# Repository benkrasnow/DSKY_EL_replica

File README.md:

# DSKY_EL_replica
Schematic, PCB layout, mechanical CAD, and firmware to create a replica of the DSKY with electroluminescent display
https://www.youtube.com/watch?v=Z2o_Sp2-aBo

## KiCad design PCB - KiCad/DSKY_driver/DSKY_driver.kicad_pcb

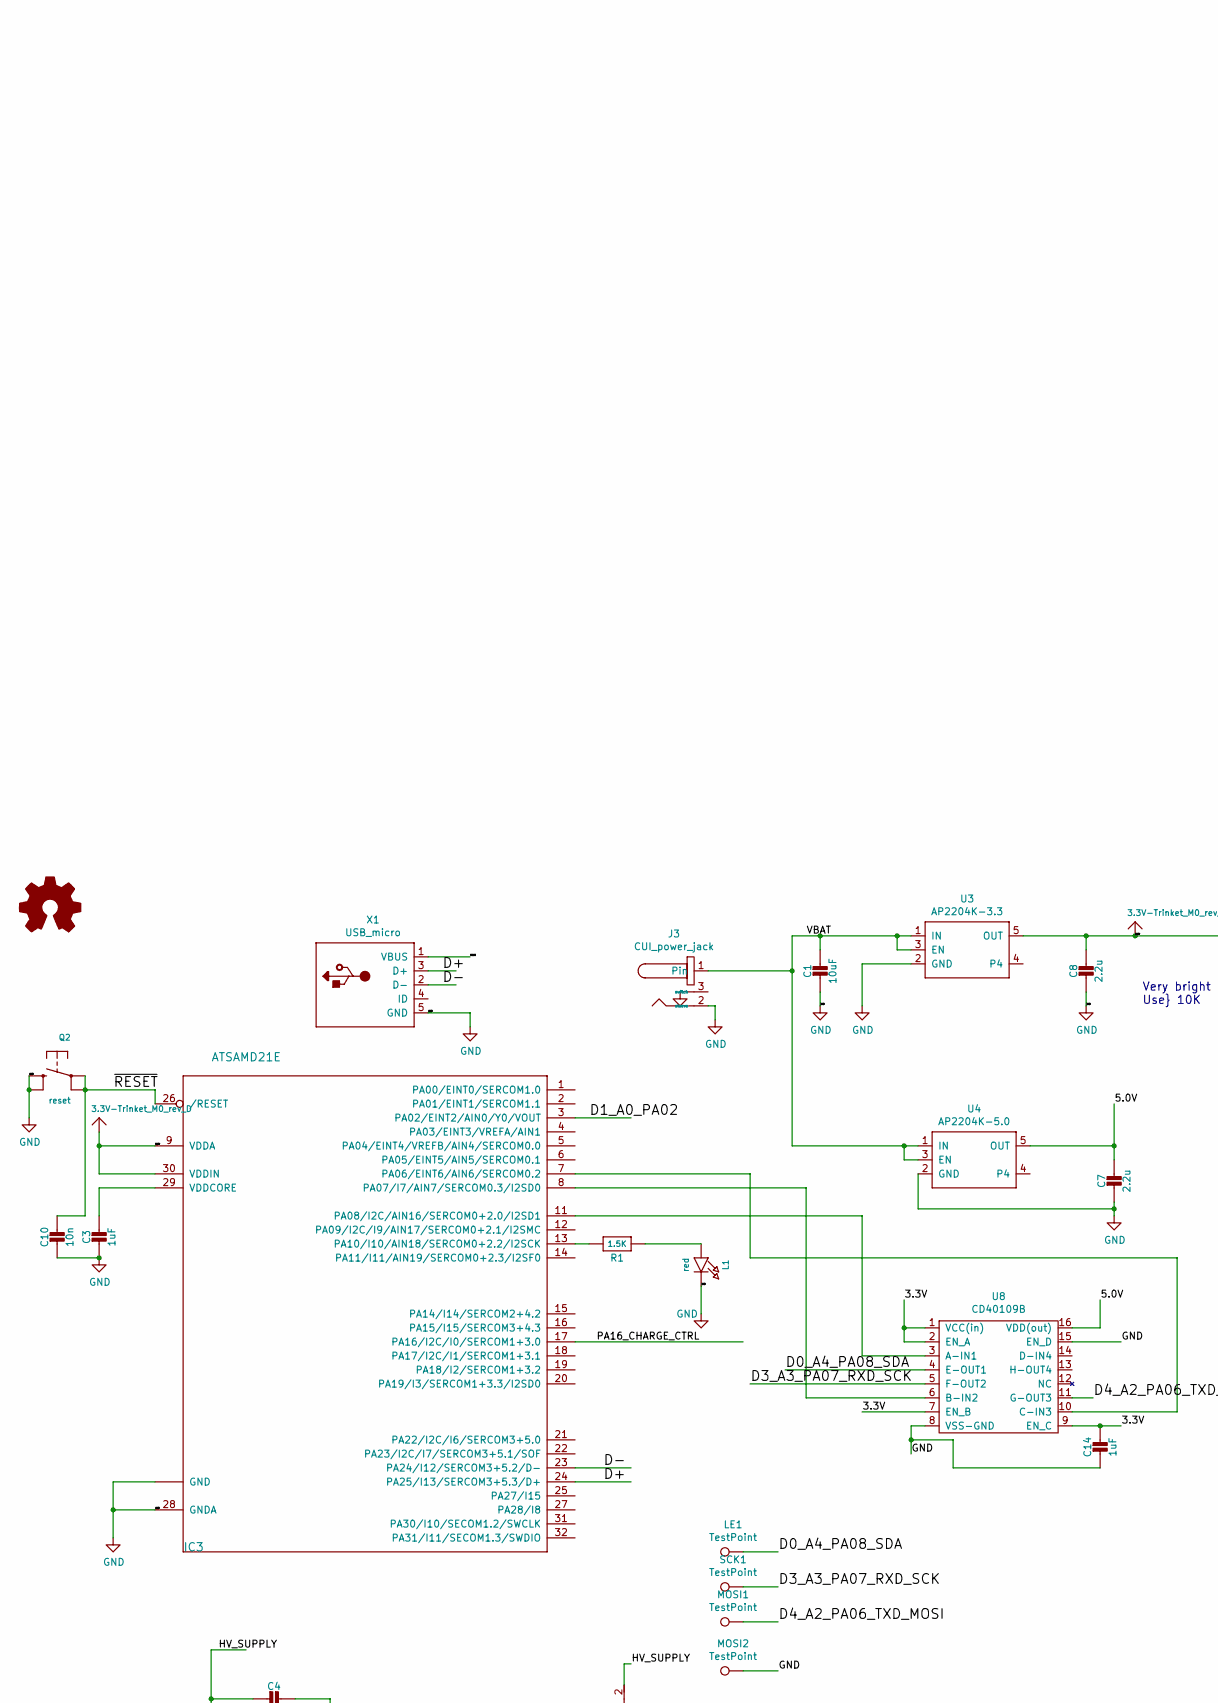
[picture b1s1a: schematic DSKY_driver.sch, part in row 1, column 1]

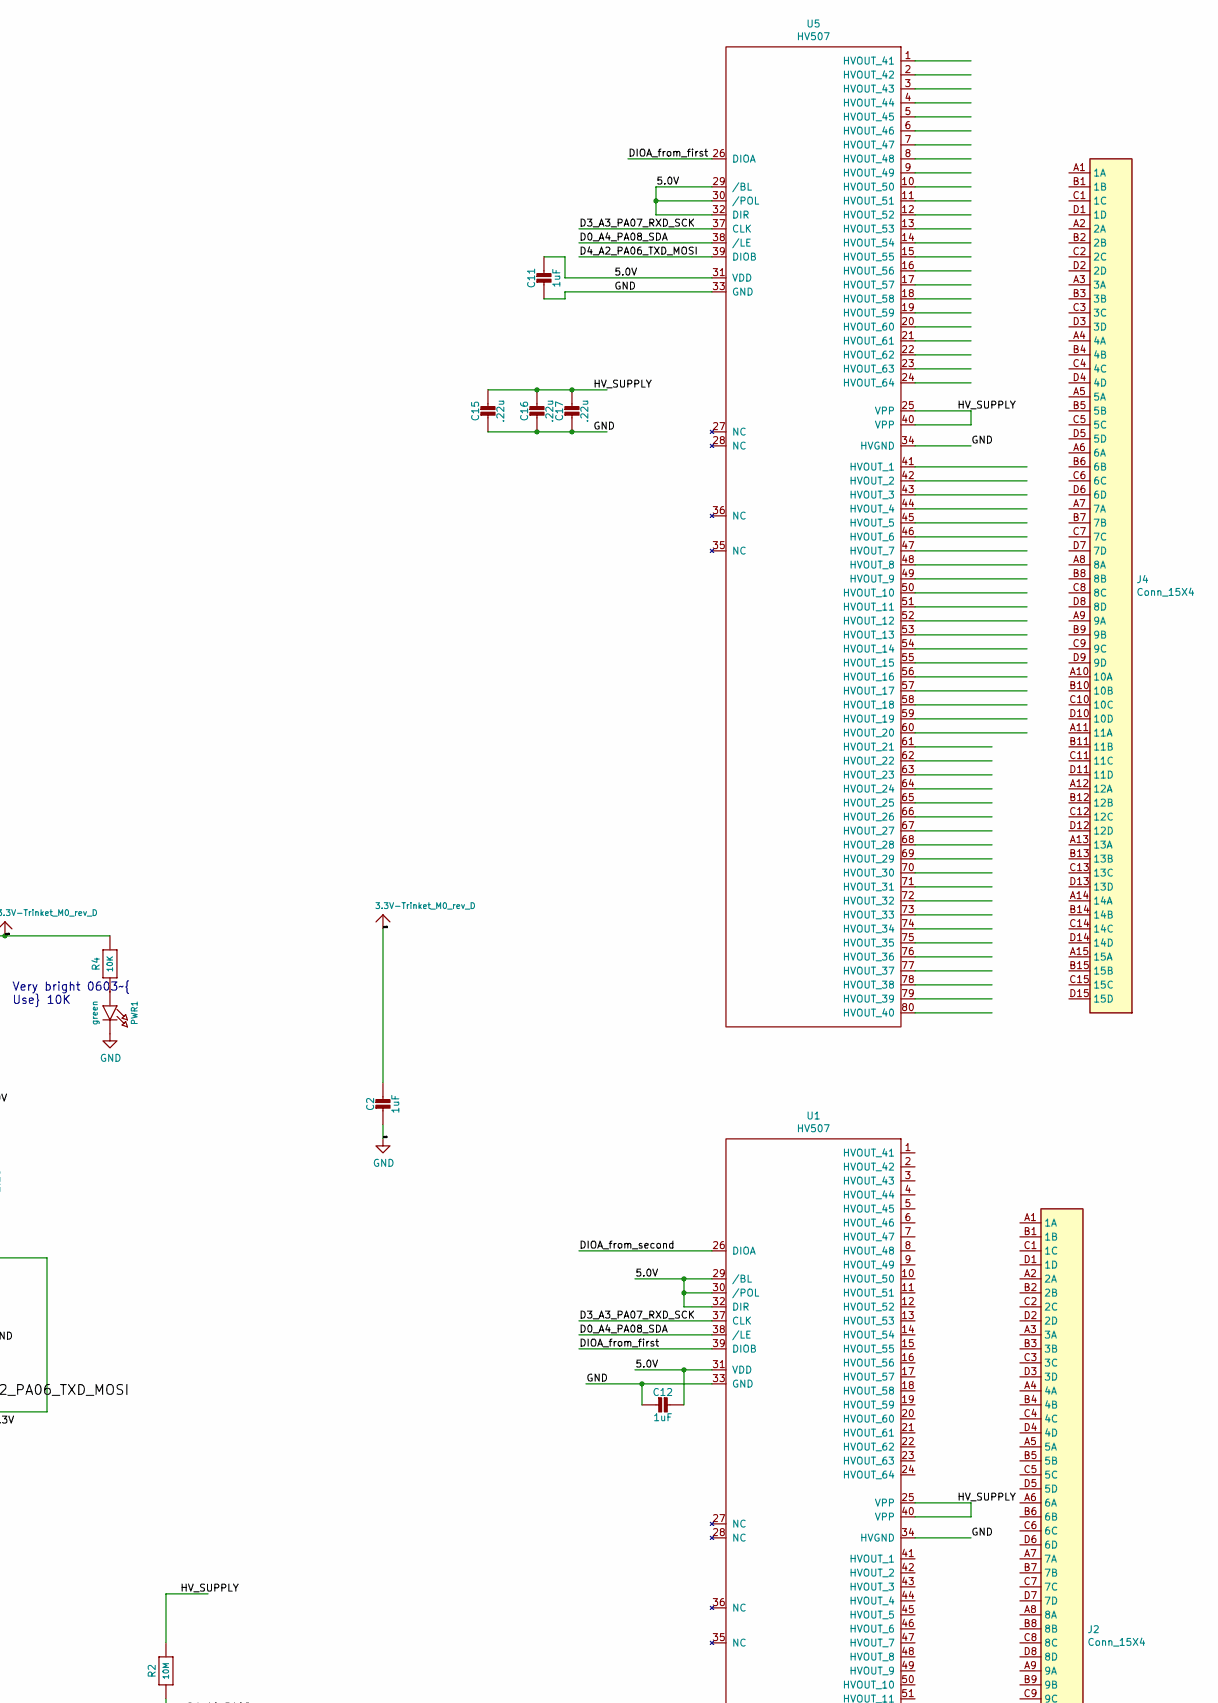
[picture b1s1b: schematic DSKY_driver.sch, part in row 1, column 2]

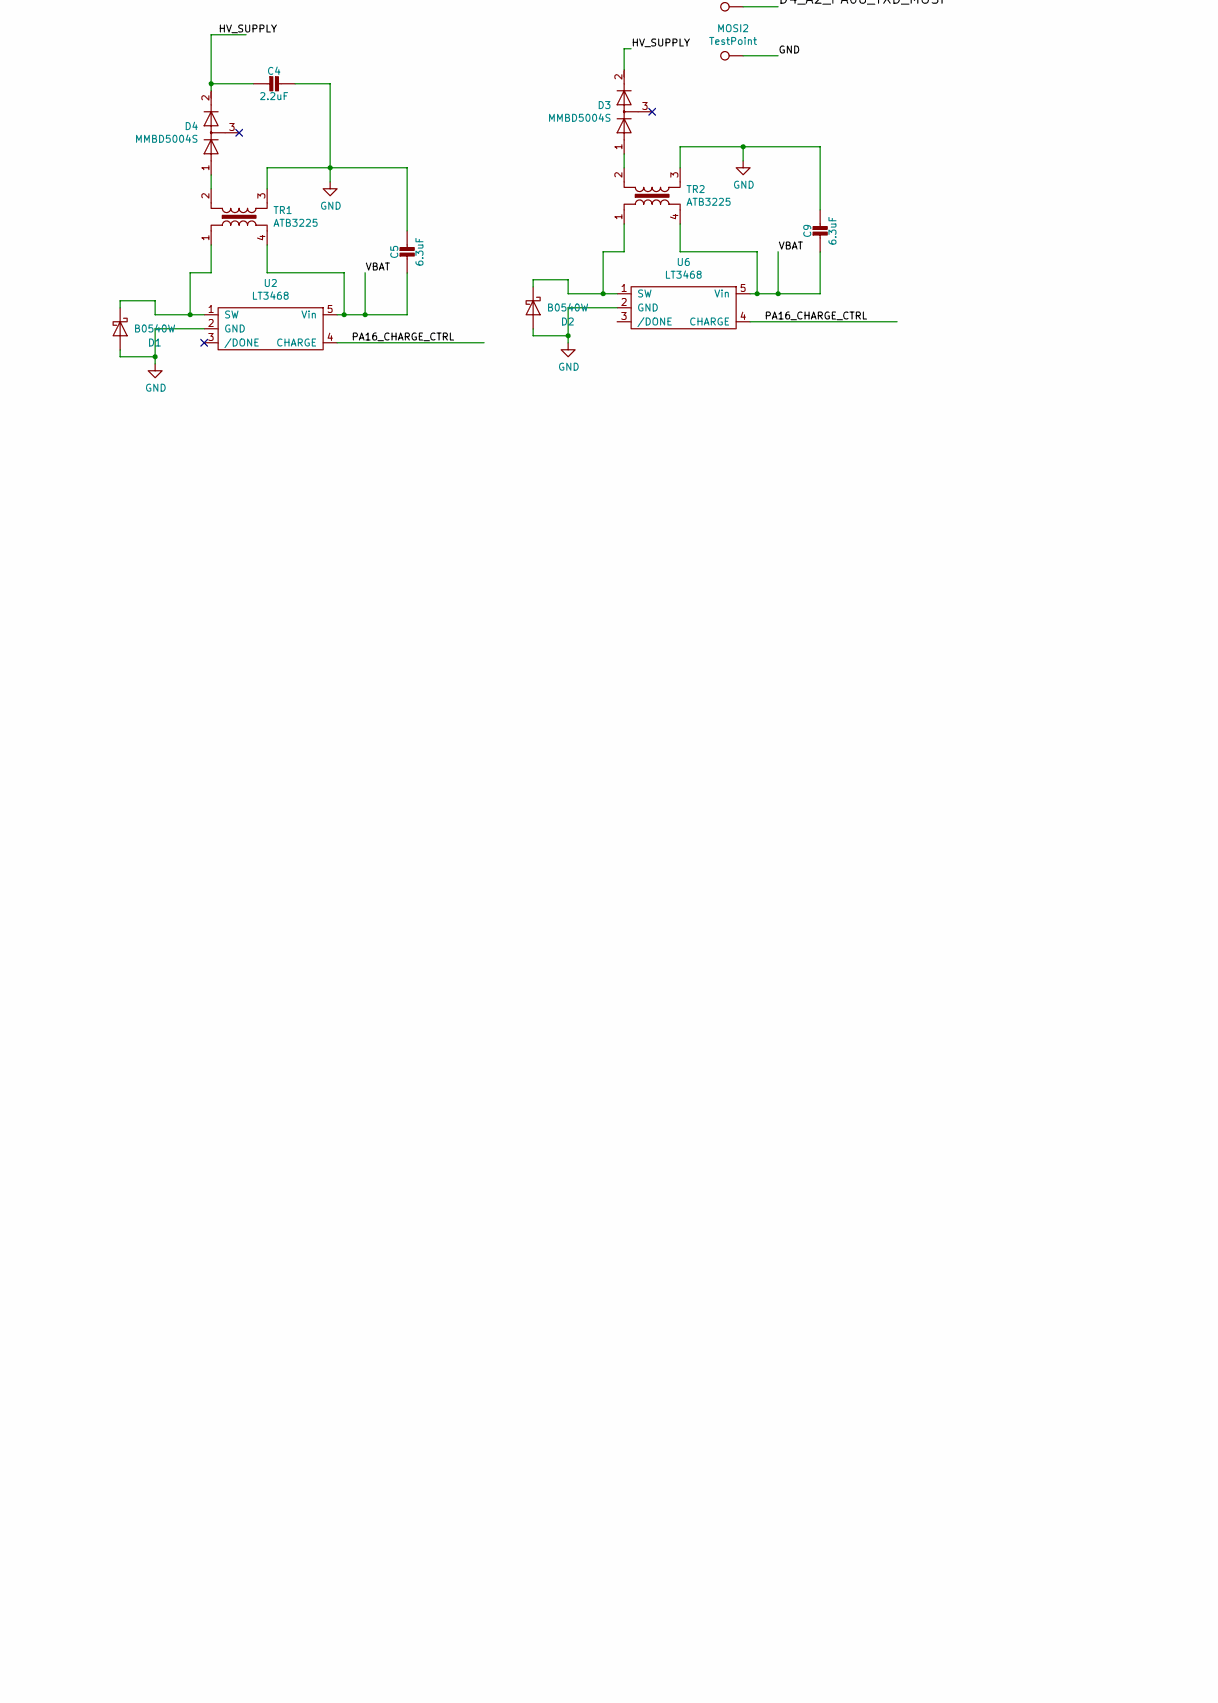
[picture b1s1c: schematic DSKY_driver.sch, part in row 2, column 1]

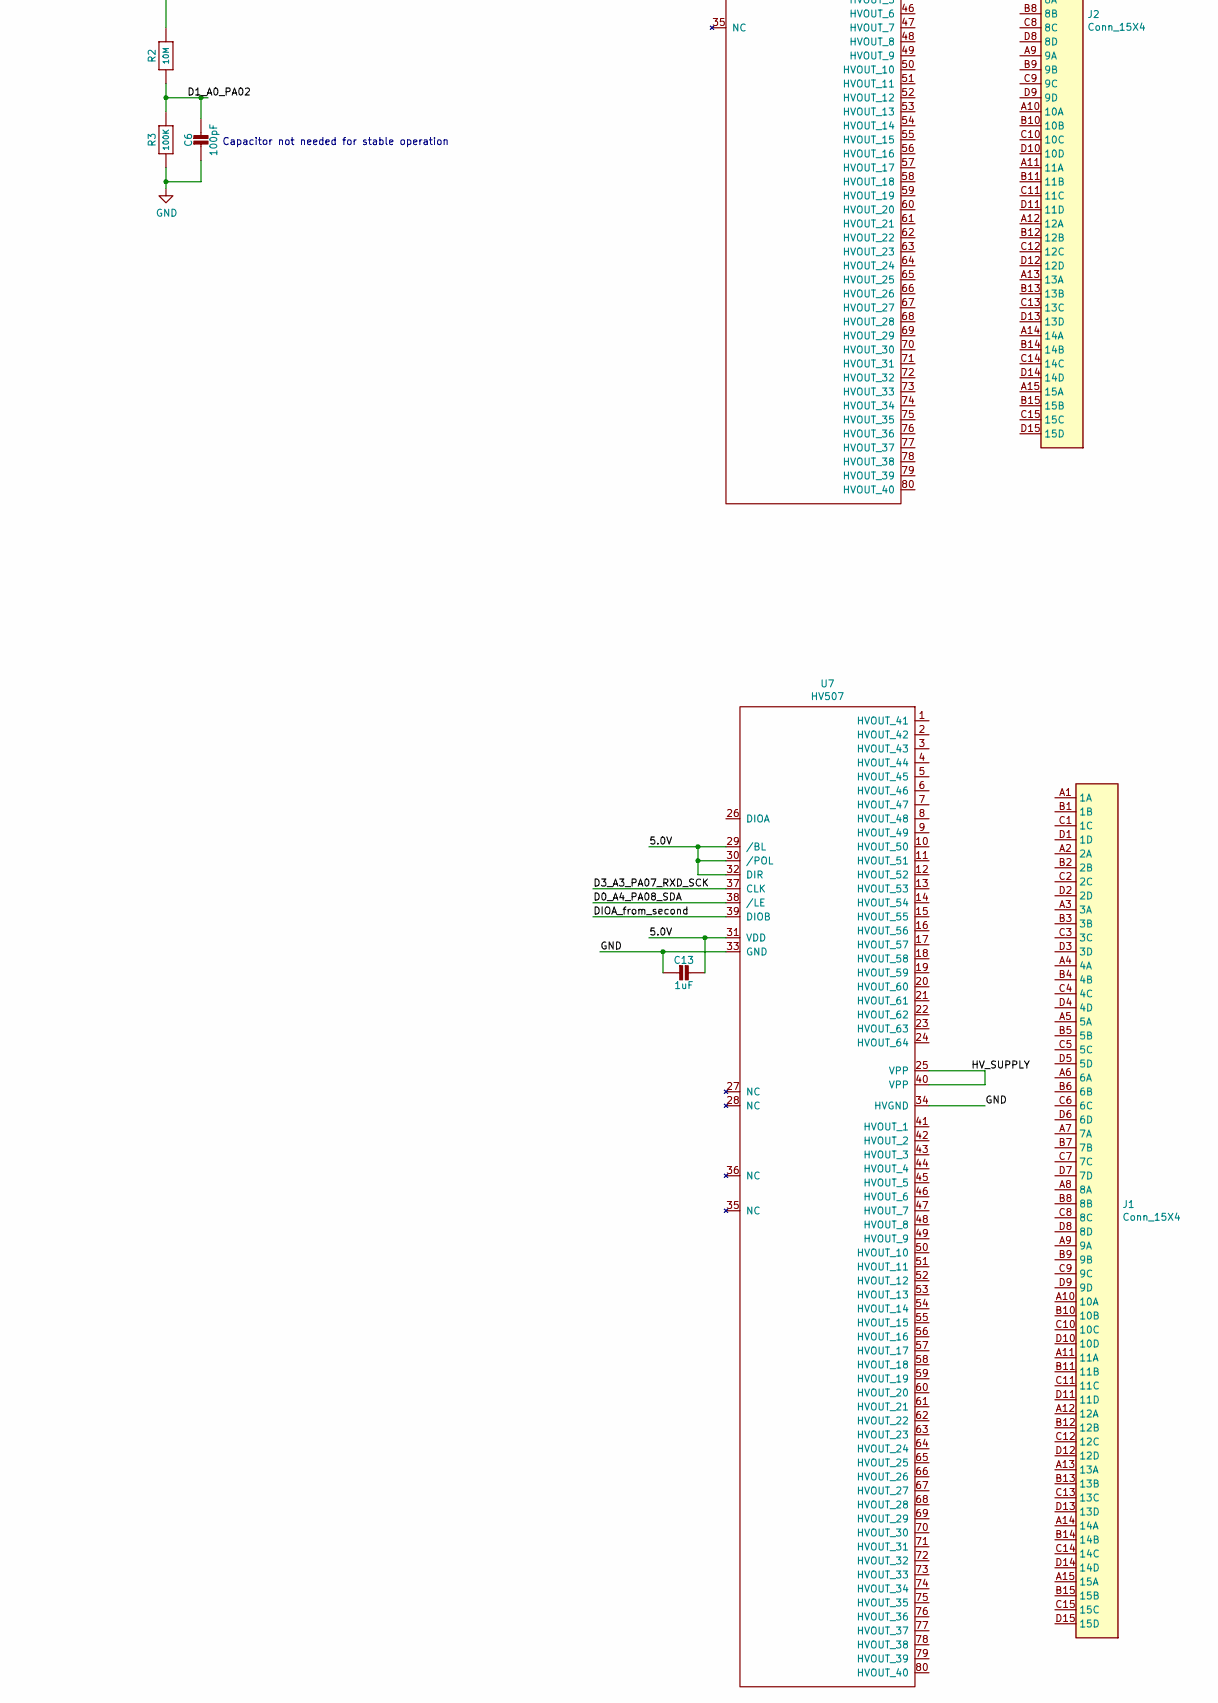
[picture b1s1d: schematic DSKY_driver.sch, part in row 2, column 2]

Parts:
C1: 10uF; 0805-NO
C2, C3, C11, C12, C13, C14: 1uF; 0603-NO
C4: 2.2uF; C_2220_5650Metric
C5, C9: 6.3uF; 0603-NO
C6: 100pF; 0603-NO
C7, C8: 2.2u; 0805-NO
C10: 10n; 0603-NO
C15, C16, C17: .22u; C_1210_3225Metric
D1, D2: B0540W; D_SOD-123
D3, D4: MMBD5004S; SOT-23
IC3: ATSAMD21E; QFN32_5MM
J1, J2, J4: Conn_15X4; FX6-60S
J3: CUI_power_jack; CUI_PJ-006B-SMT_power_jack
L1: red; CHIPLED_0603_NOOUTLINE
LE1: TestPoint; TestPoint_Pad_D1.0mm
LOGO1: Logo_Open_Hardware_Small; OSHW-Logo_5.7x6mm_SilkScreen
MOSI1, MOSI2: TestPoint; TestPoint_Pad_D1.0mm
PWR1: green; CHIPLED_0603_NOOUTLINE
Q2: reset; BTN_KMR2_4.6X2.8
R1: 1.5K; 0603-NO
R2: 10M; 0603-NO
R3: 100K; 0603-NO
R4: 10K; 0603-NO
SCK1: TestPoint; TestPoint_Pad_D1.0mm
TR1, TR2: ATB3225
U1, U5, U7: HV507; QFP-96_14x20_Pitch0.8mm
U2, U6: LT3468; SOT-23-5
U3: AP2204K-3.3; SOT-23-5
U4: AP2204K-5.0; SOT-23-5
U8: CD40109B; TSSOP-16_4.4x5mm_P0.65mm
X1: USB_micro; molex_105133_vertical_USB

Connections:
3.3V: C2.1, C8.1, C14.1, IC3.9 (VDDA), IC3.30 (VDDIN), R4.2, U3.5 (OUT), U8.1 (VCC(in)), U8.2 (EN_A), U8.7 (EN_B), U8.9 (EN_C)
/5.0V: C7.1, C11.1, C12.1, C13.1, U1.29 (/BL), U1.30 (/POL), U1.31 (VDD), U1.32 (DIR), U4.5 (OUT), U5.29 (/BL), U5.30 (/POL), U5.31 (VDD), U5.32 (DIR), U7.29 (/BL), U7.30 (/POL), U7.31 (VDD), U7.32 (DIR), U8.16 (VDD(out))
/D0_A4_PA08_SDA: LE1.1, U1.38 (/LE), U5.38 (/LE), U7.38 (/LE), U8.4 (E-OUT1); also elsewhere on the board
/D1_A0_PA02: C6.1, IC3.3 (PA02/EINT2/AIN0/Y0/VOUT), R2.1, R3.2
/D3_A3_PA07_RXD_SCK: SCK1.1, U1.37 (CLK), U5.37 (CLK), U7.37 (CLK), U8.5 (F-OUT2); also elsewhere on the board
/D4_A2_PA06_TXD_MOSI: MOSI1.1, U5.39 (DIOB), U8.11 (G-OUT3); also elsewhere on the board
/D+: IC3.24 (PA25/I13/SERCOM3+5.3/D+), X1.3 (D+)
/D-: IC3.23 (PA24/I12/SERCOM3+5.2/D-), X1.2 (D-)
/DIOA_from_first: U1.39 (DIOB), U5.26 (DIOA)
/DIOA_from_second: U1.26 (DIOA), U7.39 (DIOB)
/HV_SUPPLY: C4.2, C15.1, C16.1, C17.1, D3.2, D4.2, R2.2, U1.25 (VPP), U1.40 (VPP), U5.25 (VPP), U5.40 (VPP), U7.25 (VPP), U7.40 (VPP)
/PA16_CHARGE_CTRL: IC3.17 (PA16/I2C/I0/SERCOM1+3.0), U2.4 (CHARGE), U6.4 (CHARGE)
/VBAT: C1.1, C5.2, C9.2, J3.1, TR1.4, TR2.4, U2.5 (Vin), U3.1 (IN), U3.3 (EN), U4.1 (IN), U4.3 (EN), U6.5 (Vin)
/VBUS: X1.1 (VBUS)
/~RESET: C10.1, IC3.26 (/RESET), Q2.A, Q2.A' (P1)
GND: C1.2, C2.2, C3.2, C4.1, C5.1, C6.2, C7.2, C8.2, C9.1, C10.2, C11.2, C12.2, C13.2, C14.2, C15.2, C16.2, C17.2, D1.2 (A), D2.2 (A), IC3.10 (GND), IC3.28 (GNDA), IC3.33 (GND), J3.2 (sleeve), L1.C, MOSI2.1, PWR1.C, Q2.B (S), Q2.B' (S1), R3.1, TR1.3, TR2.3, U1.33 (GND), U1.34 (HVGND), U2.2 (GND), U3.2 (GND), U4.2 (GND), U5.33 (GND), U5.34 (HVGND), U6.2 (GND), U7.33 (GND), U7.34 (HVGND), U8.8 (VSS-GND), U8.15 (EN_D), X1.5 (GND), X1.6 (GND), X1.7 (GND), X1.8 (GND); also elsewhere on the board
unnamed: C3.1, IC3.29 (VDDCORE)
unnamed: D1.1 (K), TR1.1, U2.1 (SW)
unnamed: D2.1 (K), TR2.1, U6.1 (SW)
unnamed: D3.1, TR2.2
unnamed: D4.1, TR1.2
unnamed: IC3.7 (PA06/EINT6/AIN6/SERCOM0.2), U8.10 (C-IN3)
unnamed: IC3.8 (PA07/I7/AIN7/SERCOM0.3/I2SD0), U8.6 (B-IN2)
unnamed: IC3.11 (PA08/I2C/AIN16/SERCOM0+2.0/I2SD1), U8.3 (A-IN1)
unnamed: IC3.13 (PA10/I10/AIN18/SERCOM0+2.2/I2SCK), R1.2
unnamed: L1.A, R1.1
unnamed: PWR1.A, R4.1

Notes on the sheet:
Very bright 0603~ Use 10K
Capacitor not needed for stable operation

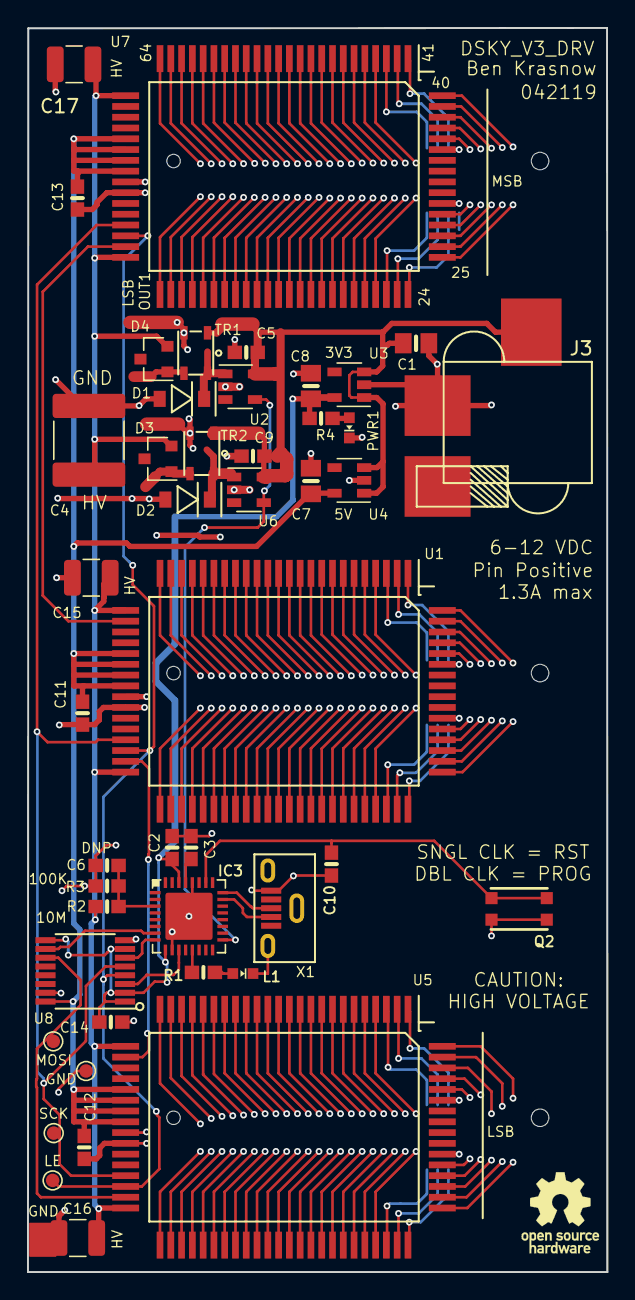
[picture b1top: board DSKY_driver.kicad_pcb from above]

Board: 2 copper layers, 43.0 x 92.3 mm, 49 parts (0 on the bottom side), 26 nets.

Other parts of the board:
GND: TestPoint; TestPoint_Pad_D1.0mm
LE: TestPoint; TestPoint_Pad_D1.0mm
MOSI: TestPoint; TestPoint_Pad_D1.0mm
SCK: TestPoint; TestPoint_Pad_D1.0mm

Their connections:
/D0_A4_PA08_SDA: LE.1; also elsewhere on the board
/D3_A3_PA07_RXD_SCK: SCK.1; also elsewhere on the board
/D4_A2_PA06_TXD_MOSI: MOSI.1; also elsewhere on the board
GND: GND.1; also elsewhere on the board

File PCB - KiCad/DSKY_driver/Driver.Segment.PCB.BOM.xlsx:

DRIVER BOARD
Verified | Designator | MFR P/N | Description | QTY | Mouser | Price | EXT | Digikey | Price | EXT
V | U1, U5, U7 | HV507PG-G | Serial to Parallel Logic Converters 325V 64Ch Push-Pull | 3.0 | 689-HV507PG-G | 14.34 | 43.02 | HV507PG-G-ND | 14.35 | 43.05
 | IC3 | ATSAMD21E18A-MUT | ARM Microcontrollers - MCU 256KB 32QFN GRN 1.6-3.6V 48MHz | 1.0 | 556-ATSAMD21E18A-MUT | 3.0 | 3 | ATSAMD21E18A-MUTCT-ND | 3.01 | 3.01
V | IC3 |  | ATSAMD21E18 Trinket M0 SAM D ARM® Cortex®-M0+ MCU 32-Bit Embedded Evaluation Bo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 | 1.0 | 485-3500 | 8.95 | 8.95 | 1528-2361-ND | 8.95 | 8.95
V | TR1, TR2 | ATB322524-0110 | Audio Transformers / Signal Transformers Photoflash Capacitor Charging Transfor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 | 2.0 | 810-ATB322524-0110 | 1.78 | 3.56 | 445-8636-1-ND | 1.98 | 3.96
V | U2, U6 | LT3468ES5#TRMPBF | Switching Voltage Regulators 500mA Photoflash Capacitor Charger | 2.0 | 584-LT3468ES5#TRMPBF | 5.06 | 10.12 | LT3468ES5#TRMPBFCT-ND | 5.07 | 10.14
V | D1, D2 | B0540W-7-F | Schottky Diodes & Rectifiers 40V 410mW | 2.0 | 621-B0540W-F | 0.39 | 0.78 | B0540W-FDICT-ND | 0.3 | 0.6
V | D3, D4 | MMBD5004S-7 | Diodes - General Purpose, Power, Switching 350MW 400V | 2.0 | 621-MMBD5004S-7 | 0.43 | 0.86 | MMBD5004S-7DICT-ND | 0.43 | 0.86
V | U8 | CD40109BPWR | Translation - Voltage Levels Quad L-H Voltage | 1.0 | 595-CD40109BPWR | 0.42 | 0.42 | 296-12163-1-ND | 0.43 | 0.43
V | U4 | AP2204K-5.0TRG1 | LDO Voltage Regulators 150mA CMOS LDO 5.0V | 1.0 | 621-AP2204K-5.0TRG1 | 0.44 | 0.44 | AP2204K-5.0TRG1DICT-ND | 0.45 | 0.45
V | U3 | AP2204K-3.3TRG1 | LDO Voltage Regulators 200mA CMOS LDO 3.3V | 1.0 | 621-AP2204K-3.3TRG1 | 0.44 | 0.44 | AP2204K-3.3TRG1DICT-ND | 0.45 | 0.45
 | R1 | RC0603FR-071K5L | Thick Film Resistors - SMD 1.5K OHM 1% | 1.0 | 603-RC0603FR-071K5L | 0.1 | 0.1 | 311-1.50KHRCT-ND | 0.1 | 0.1
 | R4 | RC0603FR-0710KL | Thick Film Resistors - SMD 10K OHM 1% | 1.0 | 603-RC0603FR-0710KL | 0.1 | 0.1 | 311-10.0KHRCT-ND | 0.1 | 0.1
 | R3 | RC0603FR-07100KL | Thick Film Resistors - SMD 100K OHM 1% | 1.0 | 603-RC0603FR-07100KL | 0.1 | 0.1 | 311-100KHRCT-ND | 0.1 | 0.1
 | R2 | RC0603FR-0710ML | Thick Film Resistors - SMD 10M OHM 1% | 1.0 | 603-RC0603FR-0710ML | 0.1 | 0.1 | 311-10.0MHRCT-ND | 0.1 | 0.1
V | C5, C9 | C1608X5R1C685K080AB | Multilayer Ceramic Capacitors MLCC - SMD/SMT 0603 16V 6.8uF X5R 10% T: 0.8mm | 2.0 | 810-C1608JB1A685K08C | 0.62 | 1.24 | 445-14139-1-ND | 0.72 | 1.44
V | C15, C16, C17 | C3225X7T2W224K200AA | Multilayer Ceramic Capacitors MLCC - SMD/SMT 1210 450V 0.22uF X7T 10% T: 2mm | 3.0 | 810-C1608X5R1C685K0B | 0.95 | 2.85 | 445-7765-1-ND | 0.73 | 2.19
V | C4 | C5750X6S2W225K250KA | Multilayer Ceramic Capacitors MLCC - SMD/SMT 2220 450V 2.2uF X6S 10% T: 2.5mm | 1.0 | 810-C5750X6S2W225KKA | 0.32 | 0.32 | 445-7781-1-ND | 3.99 | 3.99
 | C10 | C0603C103K9RACTU | Multilayer Ceramic Capacitors MLCC - SMD/SMT 6.3V 0.01uF 0603 X7R 10% | 1.0 | 80-C0603C103K9R | 0.11 | 0.11 | 399-8988-1-ND | 0.11 | 0.11
 | C14,C13,C12,C11,C2,C3 | C0603C105K8RACTU | Multilayer Ceramic Capacitors MLCC - SMD/SMT 10volts 1uF 10% X7R | 6.0 | 80-C0603C105K8R | 0.1 | 0.6 | 399-11133-1-ND | 0.1 | 0.6
 | C1,C7,C8 | 0805ZC106KAT4A | Multilayer Ceramic Capacitors MLCC - SMD/SMT 10V 10uF X7R 0805 0.1 | 3.0 | 581-0805ZC106KAT4A | 0.87 | 2.61 | 478-10578-1-ND | 0.8 | 2.4
 | C6 | 885012006008 | Multilayer Ceramic Capacitors MLCC - SMD/SMT 6.3V 100pF X7R 0603 5% | 1.0 | 710-885012006008 | 0.1 | 0.1 | 732-7752-1-ND | 0.1 | 0.1
 | Q2 | 1301.9317 | Tactile Switches SHORT TRAVEL SWITCH 6X6, 7.3MM | 1.0 | 693-1301.9317 | 0.24 | 0.24 | 486-3468-ND | 0.24 | 0.24
V | X1 | 105133-0011 | USB Connectors USB B Rec Vertical SMT 2.30 | 1.0 | 538-105133-0011 | 0.94 | 0.94 | WM10134CT-ND | 1.11 | 1.11
 | L1 | 150060RS75000 | Standard LEDs - SMD WL-SMCW SMDMono TpVw Waterclr 0603 Red | 1.0 | 710-150060RS75000 | 0.14 | 0.14 | 732-4978-1-ND | 0.14 | 0.14
 | PWR1 | 150060VS75000 | Standard LEDs - SMD WL-SMCW SMDMono TpVw Waterclr 0603 BrtGrn | 1.0 | 710-150060VS75000 | 0.14 | 0.14 | 732-4980-1-ND | 0.14 | 0.14
V | J3 | PJ-006B-SMT-TR | DC Power Connectors power jack, 2.5 x 5.5 mm, vertical, SMT, 1 switch, T&R pack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 | 1.0 | 490-PJ-006B-SMT-TR | 1.04 | 1.04 | CP-006BPJCT-ND | 1.14 | 1.14
V | J1, J2, J4 | FX6-60S-0.8SV(71) | Board to Board & Mezzanine Connectors RCP 60 POS 0.8mm Solder ST SMD Stick | 3.0 | 798-FX6-60S-0.8SV71 | 3.53 | 10.59 | H10806-ND | 3.53 | 10.59
V | P1 | WSU090-2000-13 | 100-240V WALL PLUG-IN PWR SUPPLY | 1.0 | 553-WSU090-2000-13 | 11.45 | 11.45 | 237-2263-ND | 12.39 | 12.39
ARM Chip Only |  |  |  |  |  |  | #ERROR! |  |  | #ERROR!
ARM Chip on Development Board |  |  |  |  |  |  | #ERROR! |  |  | #ERROR!
SEGMENT BOARD
V | J1, J2, J3 | FX6-60P-0.8SV(71) | Board to Board & Mezzanine Connectors HDR 60 POS 0.8mm Solder ST SMD Stick | 3.0 | 798-FX6-60P-0.8SV71 | 3.68 | 11.04 | H10787-ND | 3.68 | 11.04
V | D1 | MMBD5004S-7 | Diodes - General Purpose, Power, Switching 350MW 400V | 1.0 | 621-MMBD5004S-7 | 0.43 | 0.43 | MMBD5004S-7DICT-ND | 0.43 | 0.43
 |  |  |  |  |  |  | 11.47 |  |  | 11.47
 | Requires desoldering to obtain the chip
 | No equivalent

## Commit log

2019-04-07 Added DSKY driver PCB
2019-04-07 Added DSKY segment PCB
2019-04-07 Added mechanical CAD
2019-04-07 Added mechanical step, stl and Formlabs print file
2019-04-08 Early test code
2019-04-13 Added vector layout graphics
2019-04-13 Added version of frame with retainer to hold glass/PCB
2019-04-16 Added .form Formlabs print files
2019-04-16 Modified layout to support common electrode
2019-04-16 Shrink PCB outline
2019-04-16 Added display stackup materials and sources
2019-04-16 Added screen print supplies
2019-04-22 V3 of PCB hardware
    3.3 to 5V level shifter added
    Added decoupling caps to 5V rail and HV rail
    Added cap to RESET line
    Fixed locating holes in FX6 footprint
    Fixed unintentional trace overlap
    Eliminated the "GND" feature, and re-assigned all lines to be the common electrode
2019-04-30 First "real" code. Not fully baked
2019-05-05 Feature complete
2019-05-05 Processing.org sketch to send serial data to DSKY
2019-05-06 V4 of segment PCB
    Routing fixes. Added protection diode for common electrode
2019-05-14 Added new demo mode features and updated seg decoder table
2019-05-14 Replace 3M 9703 Z-tape with conductive epoxy
2019-05-16 Added photos of finished project
2019-05-28 Added hardware serial port functionality
    Variant.cpp must be installed in Users\[user]\AppData\Local\Arduino15\packages\adafruit\hardware\samd\1.2.3\variants\trinket_m0 to make use of pins that are not wired on the original Adafruit Trinket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
2019-06-01 Added license
2019-06-01 Added BOM
    I didn't add digikey part numbers. Someone willing to fill it out?
2019-06-02 Added Digikey order lists
2019-06-04 Added BOM with Mouser and Digikey PNs (from TAGood827)
2020-07-07 Add 0402 size current limiting resistors. Update PCB markings
2020-07-14 Switch to project-relative pathname in DSKY_driver footprint library reference
